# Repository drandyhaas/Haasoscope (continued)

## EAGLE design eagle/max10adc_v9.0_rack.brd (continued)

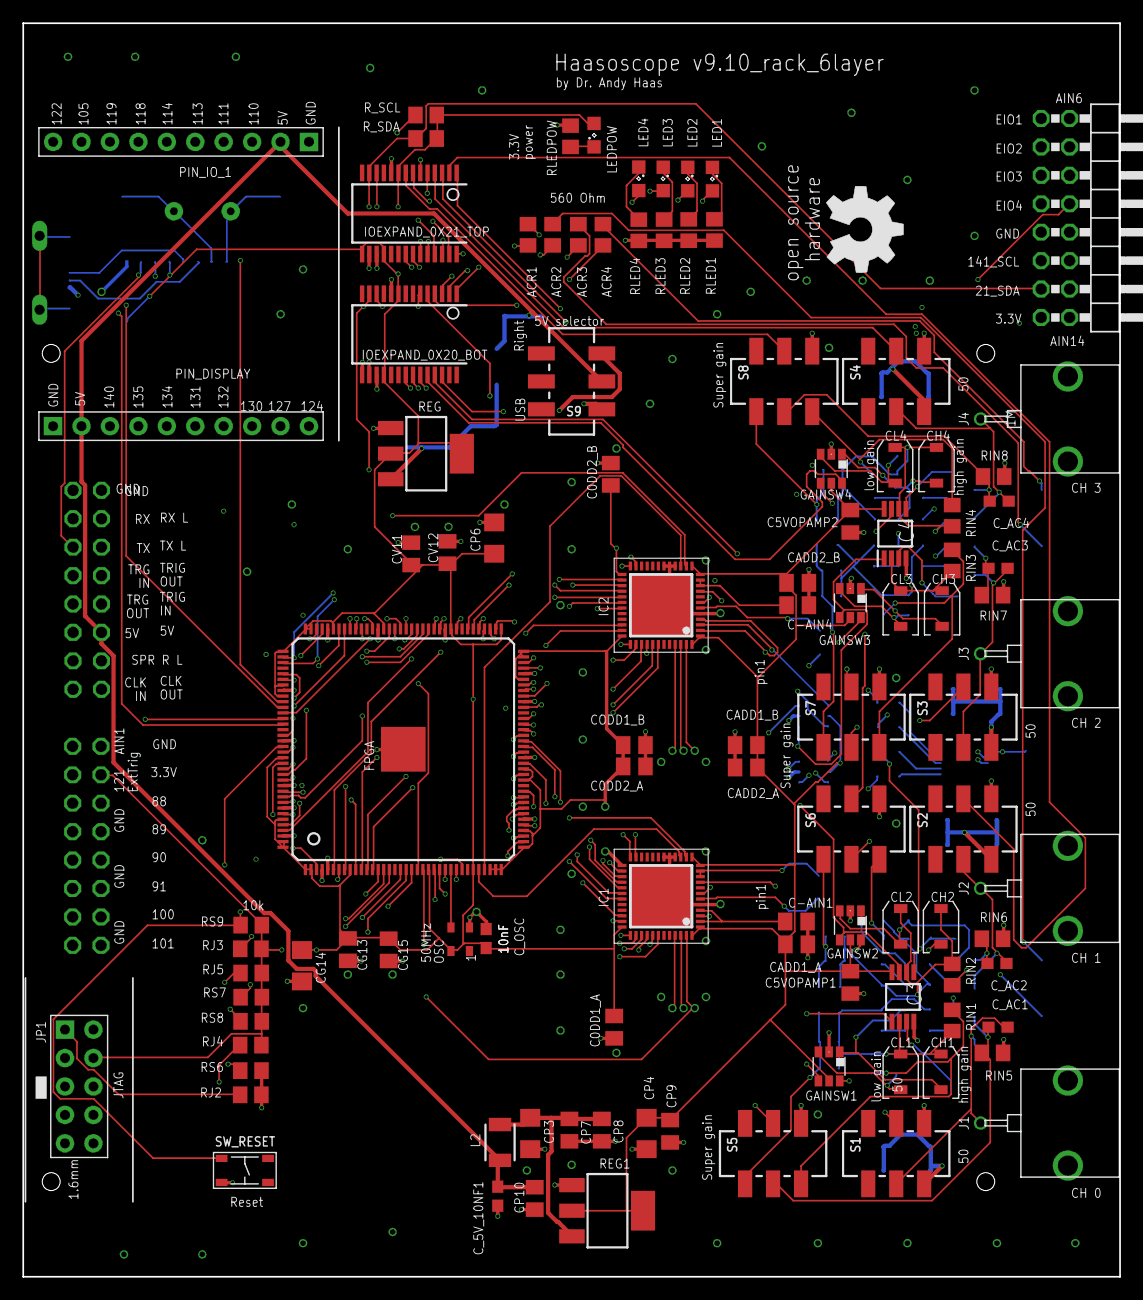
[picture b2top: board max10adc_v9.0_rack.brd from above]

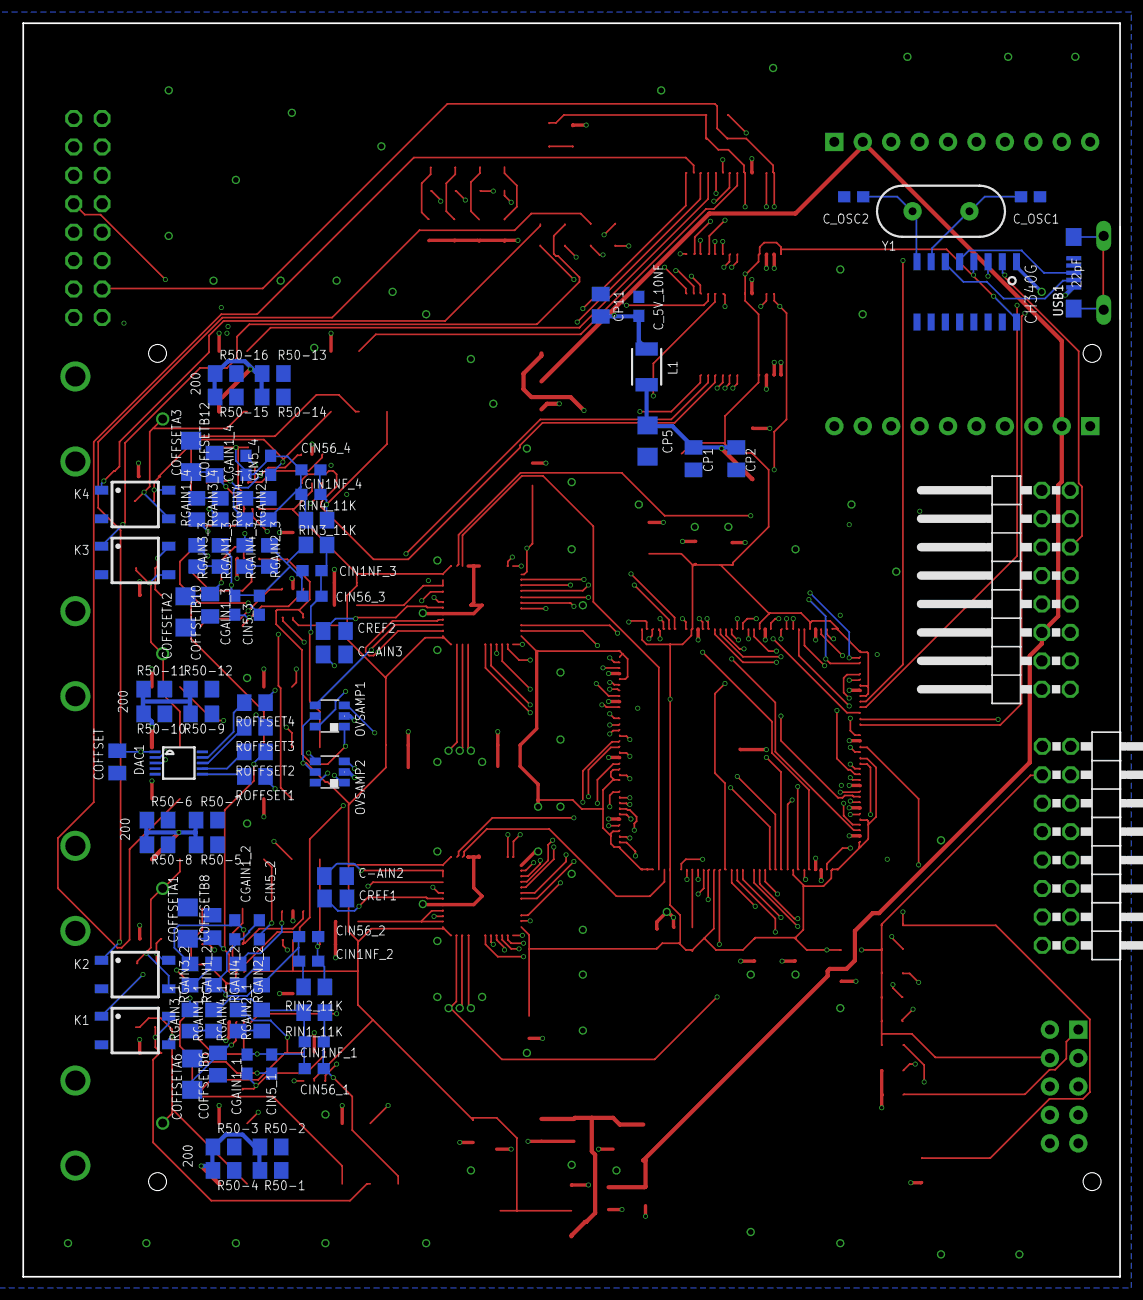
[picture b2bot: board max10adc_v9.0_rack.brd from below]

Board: 6 copper layers, 98.0 x 112.0 mm, 193 parts (89 on the bottom side), 204 nets.

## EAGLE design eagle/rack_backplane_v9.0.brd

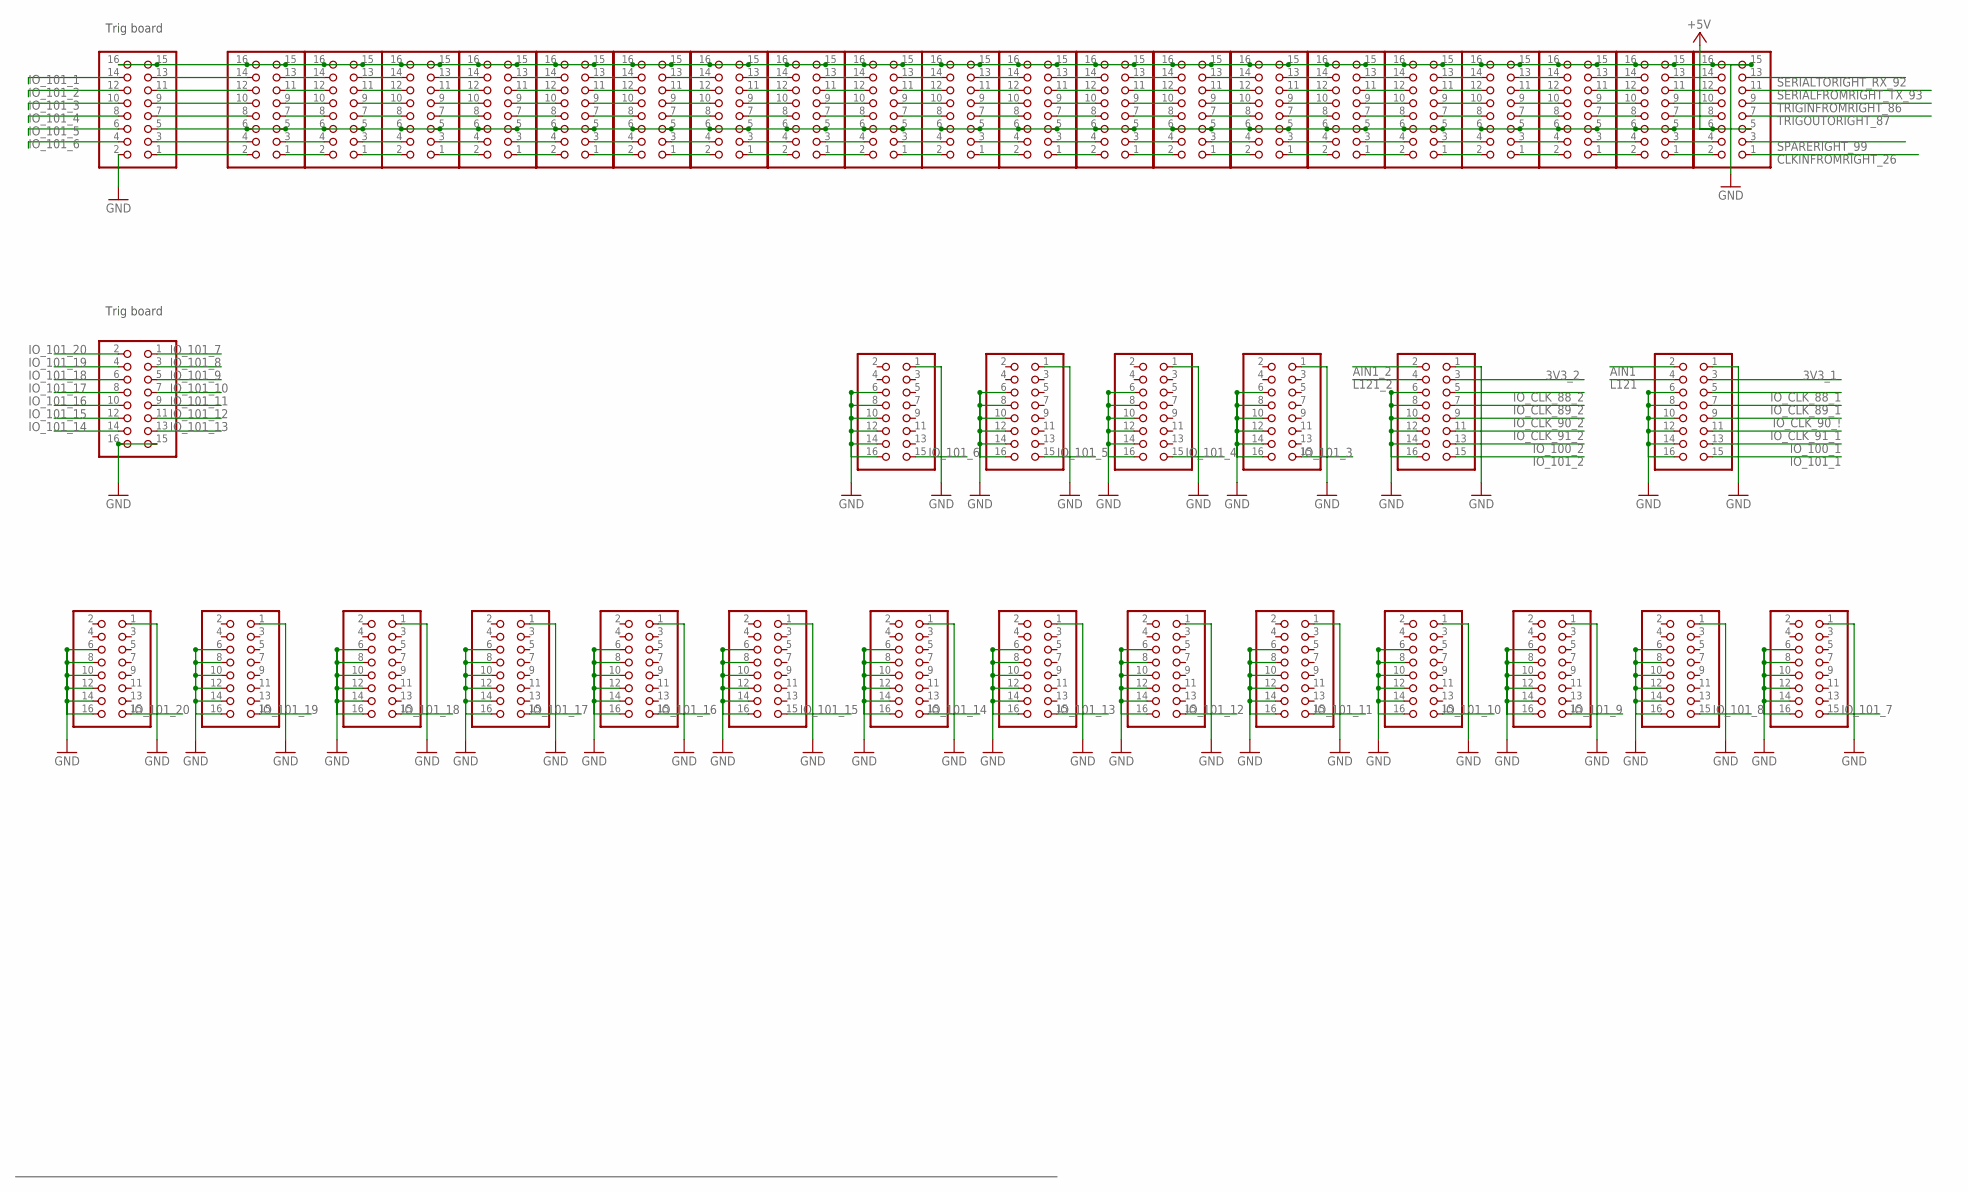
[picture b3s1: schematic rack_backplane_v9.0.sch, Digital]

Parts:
PIN_AIN_PWRGND1, PIN_AIN_PWRGND2, PIN_AIN_PWRGND3, PIN_AIN_PWRGND4, PIN_AIN_PWRGND5, PIN_AIN_PWRGND6, PIN_AIN_PWRGND7, PIN_AIN_PWRGND8, PIN_AIN_PWRGND9, PIN_AIN_PWRGND10, PIN_AIN_PWRGND11, PIN_AIN_PWRGND12, PIN_AIN_PWRGND13, PIN_AIN_PWRGND14, PIN_AIN_PWRGND15, PIN_AIN_PWRGND16, PIN_AIN_PWRGND17, PIN_AIN_PWRGND18, PIN_AIN_PWRGND19, PIN_AIN_PWRGND20, PIN_AIN_PWRGND21: 15-91-2160; 2X08; MPN 15-91-2160
PIN_ANALOG_1, PIN_ANALOG_2, PIN_ANALOG_3, PIN_ANALOG_4, PIN_ANALOG_5, PIN_ANALOG_6, PIN_ANALOG_7, PIN_ANALOG_8, PIN_ANALOG_9, PIN_ANALOG_10, PIN_ANALOG_11, PIN_ANALOG_12, PIN_ANALOG_13, PIN_ANALOG_14, PIN_ANALOG_15, PIN_ANALOG_16, PIN_ANALOG_17, PIN_ANALOG_18, PIN_ANALOG_19, PIN_ANALOG_20, PIN_ANALOG_21: 15-91-2160; 2X08; MPN 15-91-2160

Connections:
3V3_1: PIN_AIN_PWRGND1.3
3V3_2: PIN_AIN_PWRGND2.3
+5V: PIN_ANALOG_1.5, PIN_ANALOG_1.6, PIN_ANALOG_2.5, PIN_ANALOG_2.6, PIN_ANALOG_3.5, PIN_ANALOG_3.6, PIN_ANALOG_4.5, PIN_ANALOG_4.6, PIN_ANALOG_5.5, PIN_ANALOG_5.6, PIN_ANALOG_6.5, PIN_ANALOG_6.6, PIN_ANALOG_7.5, PIN_ANALOG_7.6, PIN_ANALOG_8.5, PIN_ANALOG_8.6, PIN_ANALOG_9.5, PIN_ANALOG_9.6, PIN_ANALOG_10.5, PIN_ANALOG_10.6, PIN_ANALOG_11.5, PIN_ANALOG_11.6, PIN_ANALOG_12.5, PIN_ANALOG_12.6, PIN_ANALOG_13.5, PIN_ANALOG_13.6, PIN_ANALOG_14.5, PIN_ANALOG_14.6, PIN_ANALOG_15.5, PIN_ANALOG_15.6, PIN_ANALOG_16.5, PIN_ANALOG_16.6, PIN_ANALOG_17.5, PIN_ANALOG_17.6, PIN_ANALOG_18.5, PIN_ANALOG_18.6, PIN_ANALOG_19.5, PIN_ANALOG_19.6, PIN_ANALOG_20.5, PIN_ANALOG_20.6, PIN_ANALOG_21.5
AIN1: PIN_AIN_PWRGND1.2
AIN1_2: PIN_AIN_PWRGND2.2
CLKINFROMRIGHT_26: PIN_ANALOG_1.1
GND: PIN_AIN_PWRGND1.1, PIN_AIN_PWRGND1.6, PIN_AIN_PWRGND1.8, PIN_AIN_PWRGND1.10, PIN_AIN_PWRGND1.12, PIN_AIN_PWRGND1.14, PIN_AIN_PWRGND1.16, PIN_AIN_PWRGND2.1, PIN_AIN_PWRGND2.6, PIN_AIN_PWRGND2.8, PIN_AIN_PWRGND2.10, PIN_AIN_PWRGND2.12, PIN_AIN_PWRGND2.14, PIN_AIN_PWRGND2.16, PIN_AIN_PWRGND3.1, PIN_AIN_PWRGND3.6, PIN_AIN_PWRGND3.8, PIN_AIN_PWRGND3.10, PIN_AIN_PWRGND3.12, PIN_AIN_PWRGND3.14, PIN_AIN_PWRGND3.16, PIN_AIN_PWRGND4.1, PIN_AIN_PWRGND4.6, PIN_AIN_PWRGND4.8, PIN_AIN_PWRGND4.10, PIN_AIN_PWRGND4.12, PIN_AIN_PWRGND4.14, PIN_AIN_PWRGND4.16, PIN_AIN_PWRGND5.1, PIN_AIN_PWRGND5.6, PIN_AIN_PWRGND5.8, PIN_AIN_PWRGND5.10, PIN_AIN_PWRGND5.12, PIN_AIN_PWRGND5.14, PIN_AIN_PWRGND5.16, PIN_AIN_PWRGND6.1, PIN_AIN_PWRGND6.6, PIN_AIN_PWRGND6.8, PIN_AIN_PWRGND6.10, PIN_AIN_PWRGND6.12, PIN_AIN_PWRGND6.14, PIN_AIN_PWRGND6.16, PIN_AIN_PWRGND7.1, PIN_AIN_PWRGND7.6, PIN_AIN_PWRGND7.8, PIN_AIN_PWRGND7.10, PIN_AIN_PWRGND7.12, PIN_AIN_PWRGND7.14, PIN_AIN_PWRGND7.16, PIN_AIN_PWRGND8.1, PIN_AIN_PWRGND8.6, PIN_AIN_PWRGND8.8, PIN_AIN_PWRGND8.10, PIN_AIN_PWRGND8.12, PIN_AIN_PWRGND8.14, PIN_AIN_PWRGND8.16, PIN_AIN_PWRGND9.1, PIN_AIN_PWRGND9.6, PIN_AIN_PWRGND9.8, PIN_AIN_PWRGND9.10, PIN_AIN_PWRGND9.12, PIN_AIN_PWRGND9.14, PIN_AIN_PWRGND9.16, PIN_AIN_PWRGND10.1, PIN_AIN_PWRGND10.6, PIN_AIN_PWRGND10.8, PIN_AIN_PWRGND10.10, PIN_AIN_PWRGND10.12, PIN_AIN_PWRGND10.14, PIN_AIN_PWRGND10.16, PIN_AIN_PWRGND11.1, PIN_AIN_PWRGND11.6, PIN_AIN_PWRGND11.8, PIN_AIN_PWRGND11.10, PIN_AIN_PWRGND11.12, PIN_AIN_PWRGND11.14, PIN_AIN_PWRGND11.16, PIN_AIN_PWRGND12.1, PIN_AIN_PWRGND12.6, PIN_AIN_PWRGND12.8, PIN_AIN_PWRGND12.10, PIN_AIN_PWRGND12.12, PIN_AIN_PWRGND12.14, PIN_AIN_PWRGND12.16, PIN_AIN_PWRGND13.1, PIN_AIN_PWRGND13.6, PIN_AIN_PWRGND13.8, PIN_AIN_PWRGND13.10, PIN_AIN_PWRGND13.12, PIN_AIN_PWRGND13.14, PIN_AIN_PWRGND13.16, PIN_AIN_PWRGND14.1, PIN_AIN_PWRGND14.6, PIN_AIN_PWRGND14.8, PIN_AIN_PWRGND14.10, PIN_AIN_PWRGND14.12, PIN_AIN_PWRGND14.14, PIN_AIN_PWRGND14.16, PIN_AIN_PWRGND15.1, PIN_AIN_PWRGND15.6, PIN_AIN_PWRGND15.8, PIN_AIN_PWRGND15.10, PIN_AIN_PWRGND15.12, PIN_AIN_PWRGND15.14, PIN_AIN_PWRGND15.16, PIN_AIN_PWRGND16.1, PIN_AIN_PWRGND16.6, PIN_AIN_PWRGND16.8, PIN_AIN_PWRGND16.10, PIN_AIN_PWRGND16.12, PIN_AIN_PWRGND16.14, PIN_AIN_PWRGND16.16, PIN_AIN_PWRGND17.1, PIN_AIN_PWRGND17.6, PIN_AIN_PWRGND17.8, PIN_AIN_PWRGND17.10, PIN_AIN_PWRGND17.12, PIN_AIN_PWRGND17.14, PIN_AIN_PWRGND17.16, PIN_AIN_PWRGND18.1, PIN_AIN_PWRGND18.6, PIN_AIN_PWRGND18.8, PIN_AIN_PWRGND18.10, PIN_AIN_PWRGND18.12, PIN_AIN_PWRGND18.14, PIN_AIN_PWRGND18.16, PIN_AIN_PWRGND19.1, PIN_AIN_PWRGND19.6, PIN_AIN_PWRGND19.8, PIN_AIN_PWRGND19.10, PIN_AIN_PWRGND19.12, PIN_AIN_PWRGND19.14, PIN_AIN_PWRGND19.16, PIN_AIN_PWRGND20.1, PIN_AIN_PWRGND20.6, PIN_AIN_PWRGND20.8, PIN_AIN_PWRGND20.10, PIN_AIN_PWRGND20.12, PIN_AIN_PWRGND20.14, PIN_AIN_PWRGND20.16, PIN_AIN_PWRGND21.15, PIN_AIN_PWRGND21.16, PIN_ANALOG_1.15, PIN_ANALOG_1.16, PIN_ANALOG_2.15, PIN_ANALOG_2.16, PIN_ANALOG_3.15, PIN_ANALOG_3.16, PIN_ANALOG_4.15, PIN_ANALOG_4.16, PIN_ANALOG_5.15, PIN_ANALOG_5.16, PIN_ANALOG_6.15, PIN_ANALOG_6.16, PIN_ANALOG_7.15, PIN_ANALOG_7.16, PIN_ANALOG_8.15, PIN_ANALOG_8.16, PIN_ANALOG_9.15, PIN_ANALOG_9.16, PIN_ANALOG_10.15, PIN_ANALOG_10.16, PIN_ANALOG_11.15, PIN_ANALOG_11.16, PIN_ANALOG_12.15, PIN_ANALOG_12.16, PIN_ANALOG_13.15, PIN_ANALOG_13.16, PIN_ANALOG_14.15, PIN_ANALOG_14.16, PIN_ANALOG_15.15, PIN_ANALOG_15.16, PIN_ANALOG_16.15, PIN_ANALOG_16.16, PIN_ANALOG_17.15, PIN_ANALOG_17.16, PIN_ANALOG_18.15, PIN_ANALOG_18.16, PIN_ANALOG_19.15, PIN_ANALOG_19.16, PIN_ANALOG_20.15, PIN_ANALOG_20.16, PIN_ANALOG_21.2, PIN_ANALOG_21.15, PIN_ANALOG_21.16
IO_100_1: PIN_AIN_PWRGND1.13
IO_100_2: PIN_AIN_PWRGND2.13
IO_101_1: PIN_AIN_PWRGND1.15, PIN_ANALOG_21.14
IO_101_2: PIN_AIN_PWRGND2.15, PIN_ANALOG_21.12
IO_101_3: PIN_AIN_PWRGND3.15, PIN_ANALOG_21.10
IO_101_4: PIN_AIN_PWRGND4.15, PIN_ANALOG_21.8
IO_101_5: PIN_AIN_PWRGND5.15, PIN_ANALOG_21.6
IO_101_6: PIN_AIN_PWRGND6.15, PIN_ANALOG_21.4
IO_101_7: PIN_AIN_PWRGND7.15, PIN_AIN_PWRGND21.1
IO_101_8: PIN_AIN_PWRGND8.15, PIN_AIN_PWRGND21.3
IO_101_9: PIN_AIN_PWRGND9.15, PIN_AIN_PWRGND21.5
IO_101_10: PIN_AIN_PWRGND10.15, PIN_AIN_PWRGND21.7
IO_101_11: PIN_AIN_PWRGND11.15, PIN_AIN_PWRGND21.9
IO_101_12: PIN_AIN_PWRGND12.15, PIN_AIN_PWRGND21.11
IO_101_13: PIN_AIN_PWRGND13.15, PIN_AIN_PWRGND21.13
IO_101_14: PIN_AIN_PWRGND14.15, PIN_AIN_PWRGND21.14
IO_101_15: PIN_AIN_PWRGND15.15, PIN_AIN_PWRGND21.12
IO_101_16: PIN_AIN_PWRGND16.15, PIN_AIN_PWRGND21.10
IO_101_17: PIN_AIN_PWRGND17.15, PIN_AIN_PWRGND21.8
IO_101_18: PIN_AIN_PWRGND18.15, PIN_AIN_PWRGND21.6
IO_101_19: PIN_AIN_PWRGND19.15, PIN_AIN_PWRGND21.4
IO_101_20: PIN_AIN_PWRGND20.15, PIN_AIN_PWRGND21.2
IO_CLK_88_1: PIN_AIN_PWRGND1.5
IO_CLK_88_2: PIN_AIN_PWRGND2.5
IO_CLK_89_1: PIN_AIN_PWRGND1.7
IO_CLK_89_2: PIN_AIN_PWRGND2.7
IO_CLK_90_2: PIN_AIN_PWRGND2.9
IO_CLK_90_!: PIN_AIN_PWRGND1.9
IO_CLK_91_1: PIN_AIN_PWRGND1.11
IO_CLK_91_2: PIN_AIN_PWRGND2.11
L121: PIN_AIN_PWRGND1.4
L121_2: PIN_AIN_PWRGND2.4
unnamed: PIN_ANALOG_1.14, PIN_ANALOG_2.13
unnamed: PIN_ANALOG_1.12, PIN_ANALOG_2.11
unnamed: PIN_ANALOG_1.10, PIN_ANALOG_2.9
unnamed: PIN_ANALOG_1.8, PIN_ANALOG_2.7
unnamed: PIN_ANALOG_1.4, PIN_ANALOG_2.3
unnamed: PIN_ANALOG_1.2, PIN_ANALOG_2.1
unnamed: PIN_ANALOG_2.2, PIN_ANALOG_3.1
unnamed: PIN_ANALOG_2.4, PIN_ANALOG_3.3
unnamed: PIN_ANALOG_2.8, PIN_ANALOG_3.7
unnamed: PIN_ANALOG_2.10, PIN_ANALOG_3.9
unnamed: PIN_ANALOG_2.12, PIN_ANALOG_3.11
unnamed: PIN_ANALOG_2.14, PIN_ANALOG_3.13
unnamed: PIN_ANALOG_3.2, PIN_ANALOG_4.1
unnamed: PIN_ANALOG_3.4, PIN_ANALOG_4.3
unnamed: PIN_ANALOG_3.8, PIN_ANALOG_4.7
unnamed: PIN_ANALOG_3.10, PIN_ANALOG_4.9
unnamed: PIN_ANALOG_3.12, PIN_ANALOG_4.11
unnamed: PIN_ANALOG_3.14, PIN_ANALOG_4.13
unnamed: PIN_ANALOG_4.2, PIN_ANALOG_5.1
unnamed: PIN_ANALOG_4.4, PIN_ANALOG_5.3
unnamed: PIN_ANALOG_4.8, PIN_ANALOG_5.7
unnamed: PIN_ANALOG_4.10, PIN_ANALOG_5.9
unnamed: PIN_ANALOG_4.12, PIN_ANALOG_5.11
unnamed: PIN_ANALOG_4.14, PIN_ANALOG_5.13
unnamed: PIN_ANALOG_5.2, PIN_ANALOG_6.1
unnamed: PIN_ANALOG_5.4, PIN_ANALOG_6.3
unnamed: PIN_ANALOG_5.8, PIN_ANALOG_6.7
unnamed: PIN_ANALOG_5.10, PIN_ANALOG_6.9
unnamed: PIN_ANALOG_5.12, PIN_ANALOG_6.11
unnamed: PIN_ANALOG_5.14, PIN_ANALOG_6.13
unnamed: PIN_ANALOG_6.2, PIN_ANALOG_7.1
unnamed: PIN_ANALOG_6.4, PIN_ANALOG_7.3
unnamed: PIN_ANALOG_6.8, PIN_ANALOG_7.7
unnamed: PIN_ANALOG_6.10, PIN_ANALOG_7.9
unnamed: PIN_ANALOG_6.12, PIN_ANALOG_7.11
unnamed: PIN_ANALOG_6.14, PIN_ANALOG_7.13
unnamed: PIN_ANALOG_7.2, PIN_ANALOG_8.1
unnamed: PIN_ANALOG_7.4, PIN_ANALOG_8.3
unnamed: PIN_ANALOG_7.8, PIN_ANALOG_8.7
unnamed: PIN_ANALOG_7.10, PIN_ANALOG_8.9
unnamed: PIN_ANALOG_7.12, PIN_ANALOG_8.11
unnamed: PIN_ANALOG_7.14, PIN_ANALOG_8.13
unnamed: PIN_ANALOG_8.2, PIN_ANALOG_9.1
unnamed: PIN_ANALOG_8.4, PIN_ANALOG_9.3
unnamed: PIN_ANALOG_8.8, PIN_ANALOG_9.7
unnamed: PIN_ANALOG_8.10, PIN_ANALOG_9.9
unnamed: PIN_ANALOG_8.12, PIN_ANALOG_9.11
unnamed: PIN_ANALOG_8.14, PIN_ANALOG_9.13
unnamed: PIN_ANALOG_9.2, PIN_ANALOG_10.1
unnamed: PIN_ANALOG_9.4, PIN_ANALOG_10.3
unnamed: PIN_ANALOG_9.8, PIN_ANALOG_10.7
unnamed: PIN_ANALOG_9.10, PIN_ANALOG_10.9
unnamed: PIN_ANALOG_9.12, PIN_ANALOG_10.11
unnamed: PIN_ANALOG_9.14, PIN_ANALOG_10.13
unnamed: PIN_ANALOG_10.2, PIN_ANALOG_11.1
unnamed: PIN_ANALOG_10.4, PIN_ANALOG_11.3
unnamed: PIN_ANALOG_10.8, PIN_ANALOG_11.7
unnamed: PIN_ANALOG_10.10, PIN_ANALOG_11.9
unnamed: PIN_ANALOG_10.12, PIN_ANALOG_11.11
unnamed: PIN_ANALOG_10.14, PIN_ANALOG_11.13
unnamed: PIN_ANALOG_11.2, PIN_ANALOG_12.1
unnamed: PIN_ANALOG_11.4, PIN_ANALOG_12.3
unnamed: PIN_ANALOG_11.8, PIN_ANALOG_12.7
unnamed: PIN_ANALOG_11.10, PIN_ANALOG_12.9
unnamed: PIN_ANALOG_11.12, PIN_ANALOG_12.11
unnamed: PIN_ANALOG_11.14, PIN_ANALOG_12.13
unnamed: PIN_ANALOG_12.2, PIN_ANALOG_13.1
unnamed: PIN_ANALOG_12.4, PIN_ANALOG_13.3
unnamed: PIN_ANALOG_12.8, PIN_ANALOG_13.7
unnamed: PIN_ANALOG_12.10, PIN_ANALOG_13.9
unnamed: PIN_ANALOG_12.12, PIN_ANALOG_13.11
unnamed: PIN_ANALOG_12.14, PIN_ANALOG_13.13
unnamed: PIN_ANALOG_13.2, PIN_ANALOG_14.1
unnamed: PIN_ANALOG_13.4, PIN_ANALOG_14.3
unnamed: PIN_ANALOG_13.8, PIN_ANALOG_14.7
unnamed: PIN_ANALOG_13.10, PIN_ANALOG_14.9
unnamed: PIN_ANALOG_13.12, PIN_ANALOG_14.11
unnamed: PIN_ANALOG_13.14, PIN_ANALOG_14.13
unnamed: PIN_ANALOG_14.2, PIN_ANALOG_15.1
unnamed: PIN_ANALOG_14.4, PIN_ANALOG_15.3
unnamed: PIN_ANALOG_14.8, PIN_ANALOG_15.7
unnamed: PIN_ANALOG_14.10, PIN_ANALOG_15.9
unnamed: PIN_ANALOG_14.12, PIN_ANALOG_15.11
unnamed: PIN_ANALOG_14.14, PIN_ANALOG_15.13
unnamed: PIN_ANALOG_15.2, PIN_ANALOG_16.1
unnamed: PIN_ANALOG_15.4, PIN_ANALOG_16.3
unnamed: PIN_ANALOG_15.8, PIN_ANALOG_16.7
unnamed: PIN_ANALOG_15.10, PIN_ANALOG_16.9
unnamed: PIN_ANALOG_15.12, PIN_ANALOG_16.11
unnamed: PIN_ANALOG_15.14, PIN_ANALOG_16.13
unnamed: PIN_ANALOG_16.2, PIN_ANALOG_17.1
unnamed: PIN_ANALOG_16.4, PIN_ANALOG_17.3
unnamed: PIN_ANALOG_16.8, PIN_ANALOG_17.7
unnamed: PIN_ANALOG_16.10, PIN_ANALOG_17.9
unnamed: PIN_ANALOG_16.12, PIN_ANALOG_17.11
unnamed: PIN_ANALOG_16.14, PIN_ANALOG_17.13
unnamed: PIN_ANALOG_17.2, PIN_ANALOG_18.1
unnamed: PIN_ANALOG_17.4, PIN_ANALOG_18.3
unnamed: PIN_ANALOG_17.8, PIN_ANALOG_18.7
unnamed: PIN_ANALOG_17.10, PIN_ANALOG_18.9
unnamed: PIN_ANALOG_17.12, PIN_ANALOG_18.11
unnamed: PIN_ANALOG_17.14, PIN_ANALOG_18.13
unnamed: PIN_ANALOG_18.2, PIN_ANALOG_19.1
unnamed: PIN_ANALOG_18.4, PIN_ANALOG_19.3
unnamed: PIN_ANALOG_18.8, PIN_ANALOG_19.7
unnamed: PIN_ANALOG_18.10, PIN_ANALOG_19.9
unnamed: PIN_ANALOG_18.12, PIN_ANALOG_19.11
unnamed: PIN_ANALOG_18.14, PIN_ANALOG_19.13
unnamed: PIN_ANALOG_19.2, PIN_ANALOG_20.1
unnamed: PIN_ANALOG_19.4, PIN_ANALOG_20.3
unnamed: PIN_ANALOG_19.8, PIN_ANALOG_20.7
unnamed: PIN_ANALOG_19.10, PIN_ANALOG_20.9
unnamed: PIN_ANALOG_19.12, PIN_ANALOG_20.11
unnamed: PIN_ANALOG_19.14, PIN_ANALOG_20.13
unnamed: PIN_ANALOG_20.2, PIN_ANALOG_21.1
unnamed: PIN_ANALOG_20.4, PIN_ANALOG_21.3
unnamed: PIN_ANALOG_20.8, PIN_ANALOG_21.7
unnamed: PIN_ANALOG_20.10, PIN_ANALOG_21.9
unnamed: PIN_ANALOG_20.12, PIN_ANALOG_21.11
unnamed: PIN_ANALOG_20.14, PIN_ANALOG_21.13
SERIALFROMRIGHT_TX_93: PIN_ANALOG_1.11
SERIALTORIGHT_RX_92: PIN_ANALOG_1.13
SPARERIGHT_99: PIN_ANALOG_1.3
TRIGINFROMRIGHT_86: PIN_ANALOG_1.9
TRIGOUTORIGHT_87: PIN_ANALOG_1.7

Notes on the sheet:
Trig board

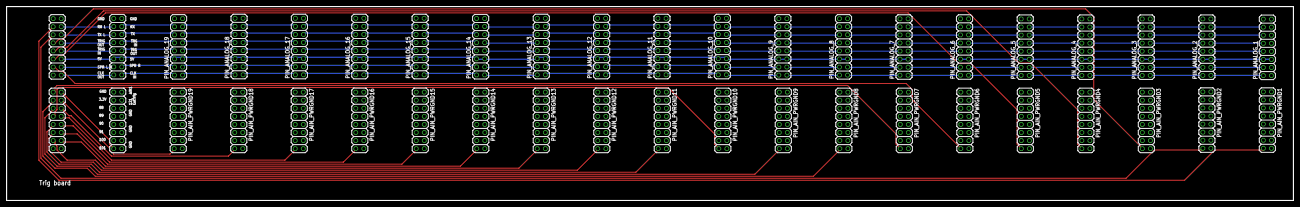
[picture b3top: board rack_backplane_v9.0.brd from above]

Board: 4 copper layers, 405.1 x 61.0 mm, 43 parts (1 on the bottom side), 142 nets.

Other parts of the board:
GOLD_ORB_SM1: OSHWLOGOLOGO8MM; OSHW_8MM
